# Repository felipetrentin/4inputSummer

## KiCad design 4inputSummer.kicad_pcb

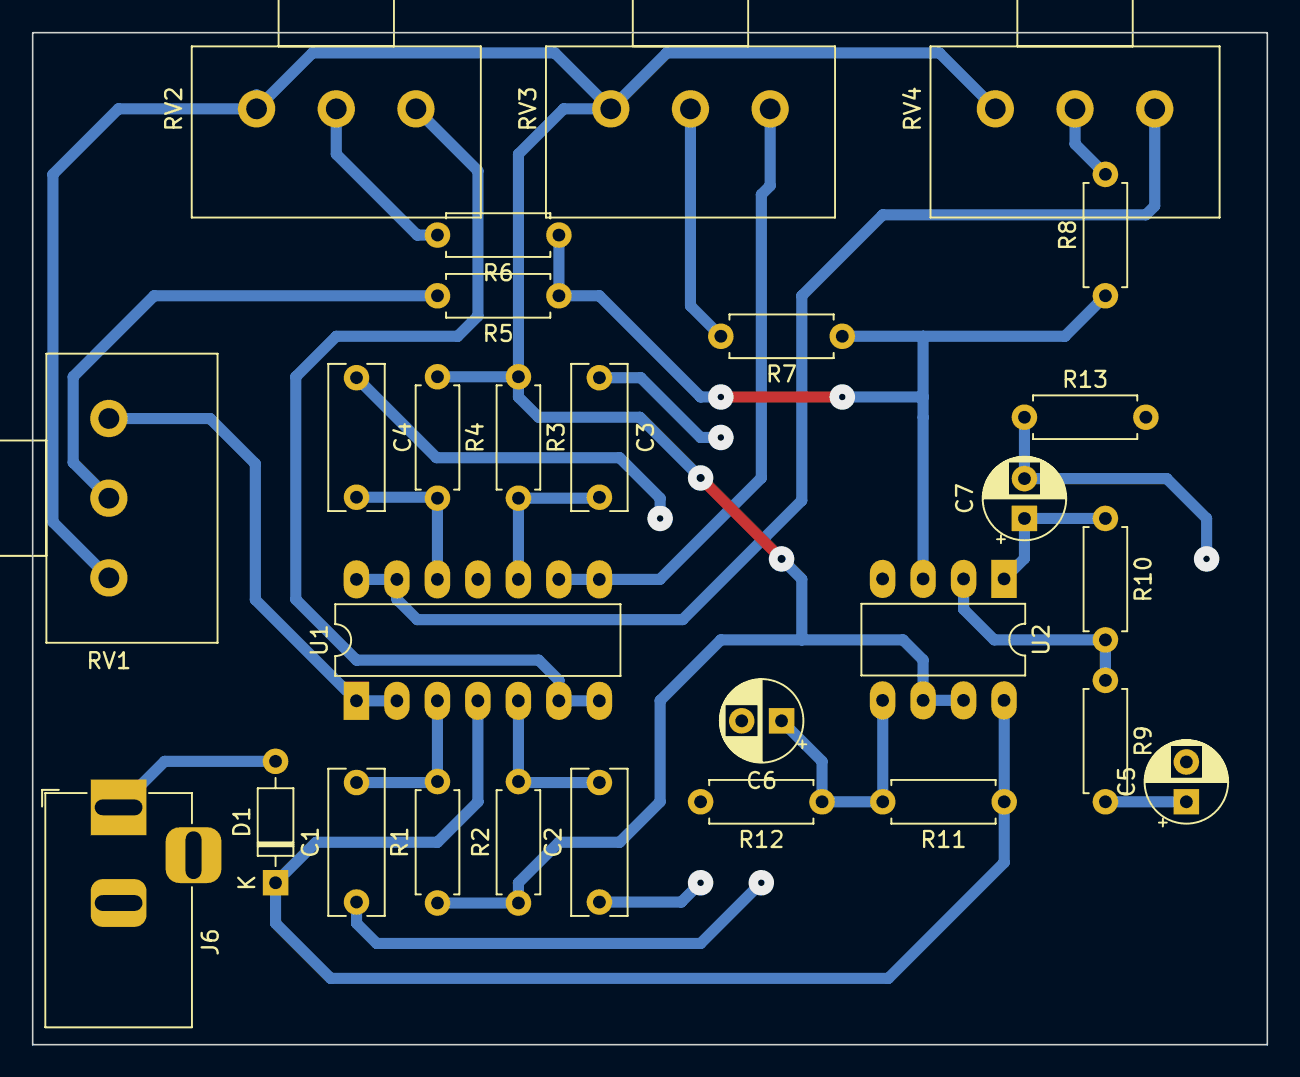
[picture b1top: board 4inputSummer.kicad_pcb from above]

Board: 2 copper layers, 77.5 x 63.5 mm, 28 parts (0 on the bottom side), 22 nets.

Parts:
C1, C2, C3, C4: 470nF; C_Rect_L9.0mm_W3.3mm_P7.50mm_MKT
C5, C6, C7: 4.7uF; CP_Radial_D5.0mm_P2.50mm
D1: 1N914; D_DO-35_SOD27_P7.62mm_Horizontal
J6: 9V PSU; BarrelJack_Horizontal
R1, R2, R3, R4: 1M; R_Axial_DIN0207_L6.3mm_D2.5mm_P7.62mm_Horizontal
R5, R6, R7, R8: 100k; R_Axial_DIN0207_L6.3mm_D2.5mm_P7.62mm_Horizontal
R9: 1k; R_Axial_DIN0207_L6.3mm_D2.5mm_P7.62mm_Horizontal
R10, R13: 10k; R_Axial_DIN0207_L6.3mm_D2.5mm_P7.62mm_Horizontal
R11, R12: 470k; R_Axial_DIN0207_L6.3mm_D2.5mm_P7.62mm_Horizontal
RV1, RV2, RV3, RV4: 10KA; Potentiometer_Alps_RK163_Single_Horizontal
U1: TL074; DIP-14_W7.62mm_LongPads
U2: TL072; DIP-8_W7.62mm_LongPads

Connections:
+9V: D1.1 (K), R11.1, U1.4 (V+), U2.8 (V+)
GND: C5.2, C6.2, J6.2, R12.2, R13.2, U1.11 (V-), U2.4 (V-)
unnamed: C1.2, R1.2, U1.3 (+)
unnamed: C2.2, R2.2, U1.5 (+)
unnamed: C3.2, R3.2, U1.10 (+)
unnamed: C4.2, R4.2, U1.12 (+)
unnamed: C5.1, R9.2
unnamed: C6.1, R11.2, R12.1, U2.5 (+)
unnamed: C7.1, R10.1, U2.1
unnamed: C7.2, R13.1
unnamed: D1.2 (A), J6.1
unnamed: R5.1, R6.1, R7.1, R8.1, U2.3 (+)
unnamed: R5.2, RV1.2
unnamed: R6.2, RV2.2
unnamed: R7.2, RV3.2
unnamed: R8.2, RV4.2
unnamed: R9.1, R10.2, U2.2 (-)
unnamed: RV1.1, U1.1, U1.2 (-)
unnamed: RV2.1, U1.6 (-), U1.7
unnamed: RV3.1, U1.8, U1.9 (-)
unnamed: RV4.1, U1.13 (-), U1.14
Vref: R1.1, R2.1, R3.1, R4.1, RV1.3, RV2.3, RV3.3, RV4.3, U2.6 (-), U2.7
